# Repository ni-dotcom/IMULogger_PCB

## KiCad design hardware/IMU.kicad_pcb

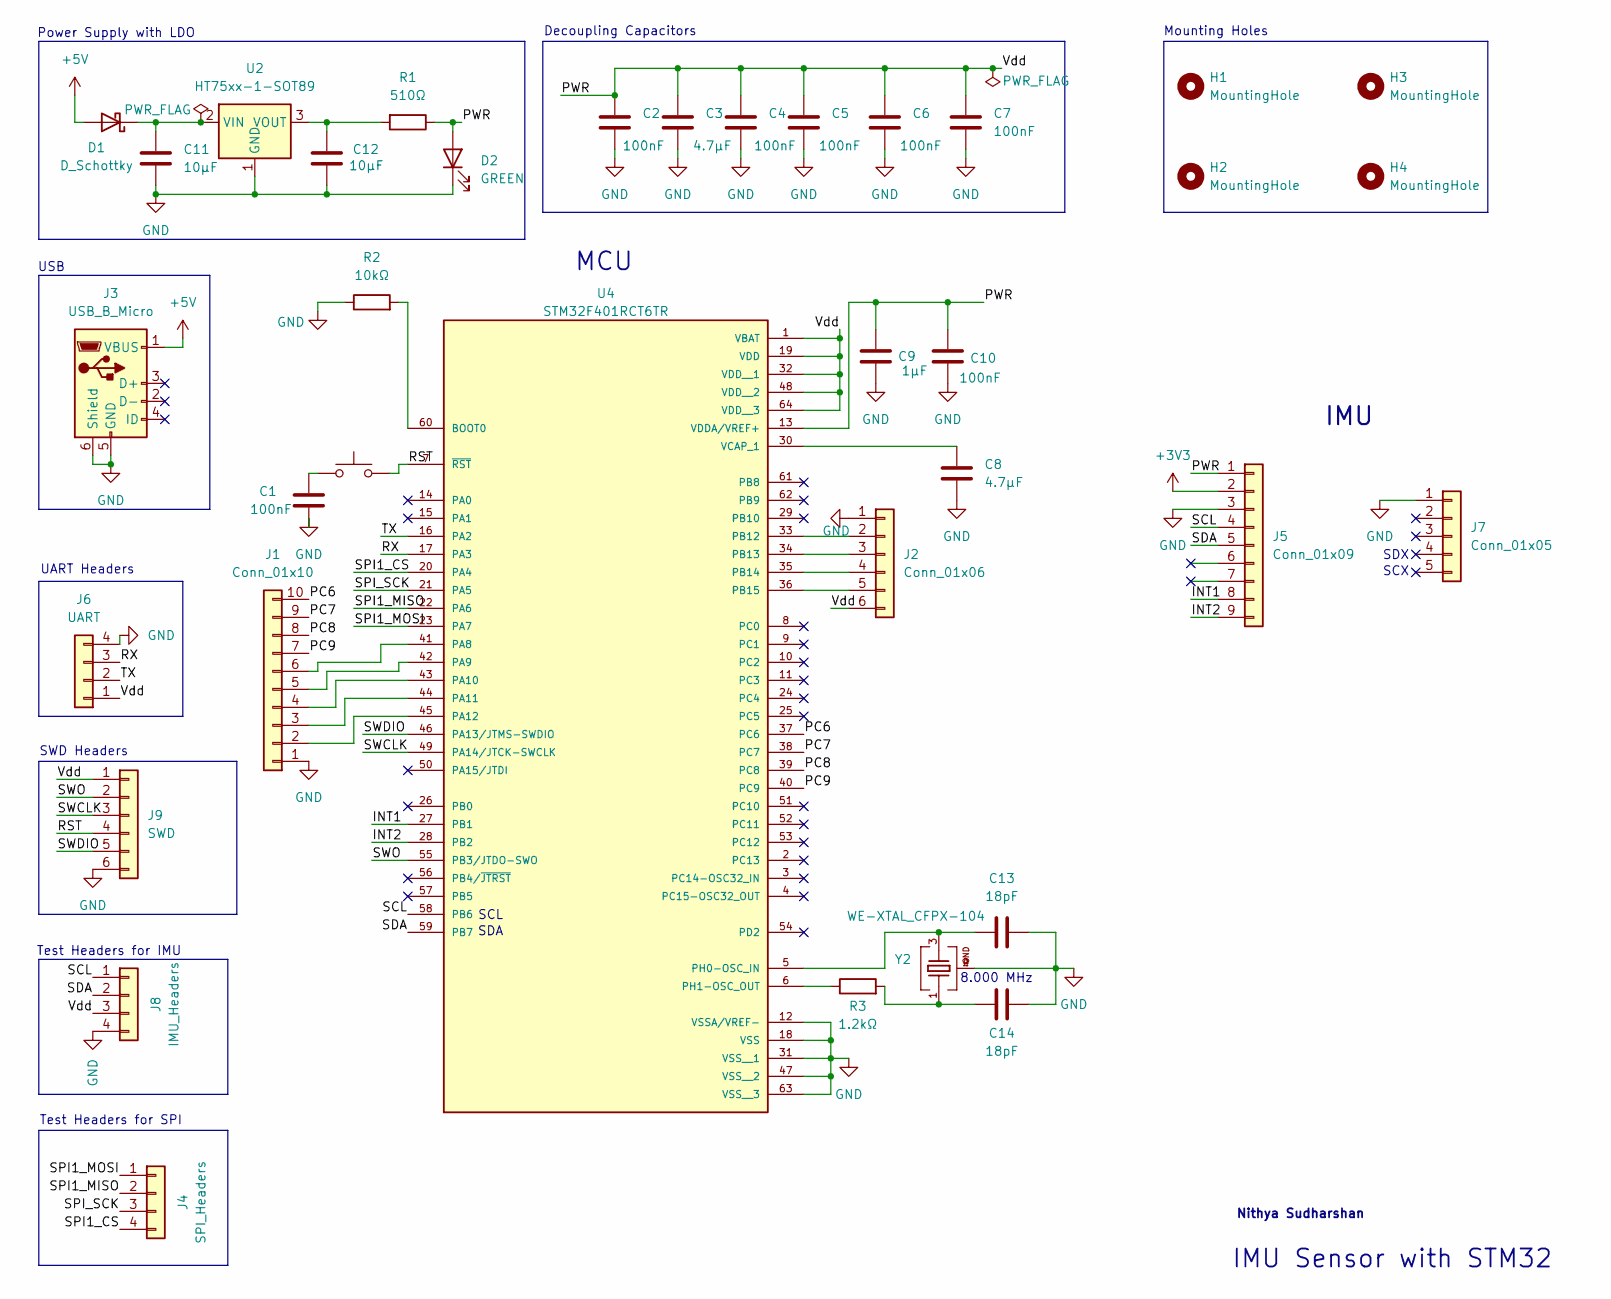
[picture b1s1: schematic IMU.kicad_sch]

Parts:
C1, C2, C4, C5, C6, C7, C10: 100nF; C_0805_2012Metric
C3, C8: 4.7μF; C_0805_2012Metric
C9: 1μF; C_0805_2012Metric
C11, C12: 10μF; C_0805_2012Metric
C13, C14: 18pF; C_0805_2012Metric
D1: D_Schottky; D_3220_8050Metric
D2: GREEN; LED_0805_2012Metric
H1, H2, H3, H4: MountingHole; MountingHole_2.7mm_M2.5_Pad
J1: Conn_01x10; PinHeader_1x10_P2.54mm_Vertical
J2: Conn_01x06; PinHeader_1x06_P2.54mm_Vertical
J3: USB_B_Micro; USB_Micro-B_GCT_USB3076-30-A
J4: SPI_Headers; PinHeader_1x04_P2.54mm_Vertical
J5: Conn_01x09; PinHeader_1x09_P2.54mm_Vertical
J6: UART; PinHeader_1x04_P2.54mm_Vertical
J7: Conn_01x05; PinHeader_1x05_P2.54mm_Vertical
J8: IMU_Headers; PinHeader_1x04_P2.54mm_Vertical
J9: SWD; PinHeader_1x06_P2.54mm_Vertical
R1: 510Ω; R_0805_2012Metric
R2: 10kΩ; R_0805_2012Metric
R3: 1.2kΩ; R_0805_2012Metric
SW1: SW_Push; SW_SPST_PTS647_Sx38
U2: HT75xx-1-SOT89; SOT-89-3
U4: STM32F401RCT6TR; STM32F4QFP50P1200X1200X160-64N; PARTREV 11
Y2: WE-XTAL_CFPX-104

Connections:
+3V3: J5.2; also elsewhere on the board
+5V: D1.2 (A), J3.1 (VBUS)
/INT1: J5.8, U4.27 (PB1)
/INT2: J5.9, U4.28 (PB2)
/PC6: J1.10, U4.37 (PC6)
/PC7: J1.9, U4.38 (PC7)
/PC8: J1.8, U4.39 (PC8)
/PC9: J1.7, U4.40 (PC9)
/PWR: C2.1, C3.1, C4.1, C5.1, C6.1, C7.1, C9.1, C10.1, D2.2 (A), J2.6, J5.1, J6.1, J8.3, J9.1, R1.1, U4.1 (VBAT), U4.13 (VDDA/VREF+), U4.19 (VDD), U4.32 (VDD__1), U4.48 (VDD__2), U4.64 (VDD__3)
/RST: J9.4, SW1.2, U4.7 (~RST)
/RX: J6.3, U4.17 (PA3)
/SCL: J5.4, J8.1, U4.58 (PB6)
/SDA: J5.5, J8.2, U4.59 (PB7)
/SPI1_CS: J4.4, U4.20 (PA4)
/SPI1_MISO: J4.2, U4.22 (PA6)
/SPI1_MOSI: J4.1, U4.23 (PA7)
/SPI_SCK: J4.3, U4.21 (PA5)
/SWCLK: J9.3, U4.49 (PA14/JTCK-SWCLK)
/SWDIO: J9.5, U4.46 (PA13/JTMS-SWDIO)
/SWO: J9.2, U4.55 (PB3/JTDO-SWO)
/TX: J6.2, U4.16 (PA2)
GND: C1.2, C2.2, C3.2, C4.2, C5.2, C6.2, C7.2, C8.2, C9.2, C10.2, C11.2, C12.2, C13.2, C14.1, D2.1 (K), J1.1, J2.1, J3.5 (GND), J3.6 (Shield), J5.3, J6.4, J7.1, J8.4, J9.6, R2.1, U2.1 (GND), U4.12 (VSSA/VREF-), U4.18 (VSS), U4.31 (VSS__1), U4.47 (VSS__2), U4.63 (VSS__3), Y2.2, Y2.4
unnamed 22: C1.1, SW1.1; also elsewhere on the board
unnamed: C14.2, R3.2, Y2.1
unnamed: C11.1, D1.1 (K), U2.2 (VIN)
unnamed: J1.2, U4.45 (PA12)
unnamed: J1.3, U4.44 (PA11)
unnamed: J1.4, U4.43 (PA10)
unnamed: J1.5, U4.42 (PA9)
unnamed: J1.6, U4.41 (PA8)
unnamed: J2.2, U4.33 (PB12)
unnamed: J2.3, U4.34 (PB13)
unnamed: J2.4, U4.35 (PB14)
unnamed: J2.5, U4.36 (PB15)
unnamed: C12.1, R1.2, U2.3 (VOUT)
unnamed: R2.2, U4.60 (BOOT0)
unnamed: C13.1, U4.5 (PH0-OSC_IN), Y2.3
unnamed: R3.1, U4.6 (PH1-OSC_OUT)
unnamed: C8.1, U4.30 (VCAP_1)

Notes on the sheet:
SDA
SCL
IMU Sensor with STM32
Mounting Holes
8.000 MHz
Power Supply with LDO
SDX
Nithya Sudharshan
SWD Headers
Test Headers for IMU
USB
MCU
SCX
Decoupling Capacitors
Test Headers for SPI
IMU
UART Headers

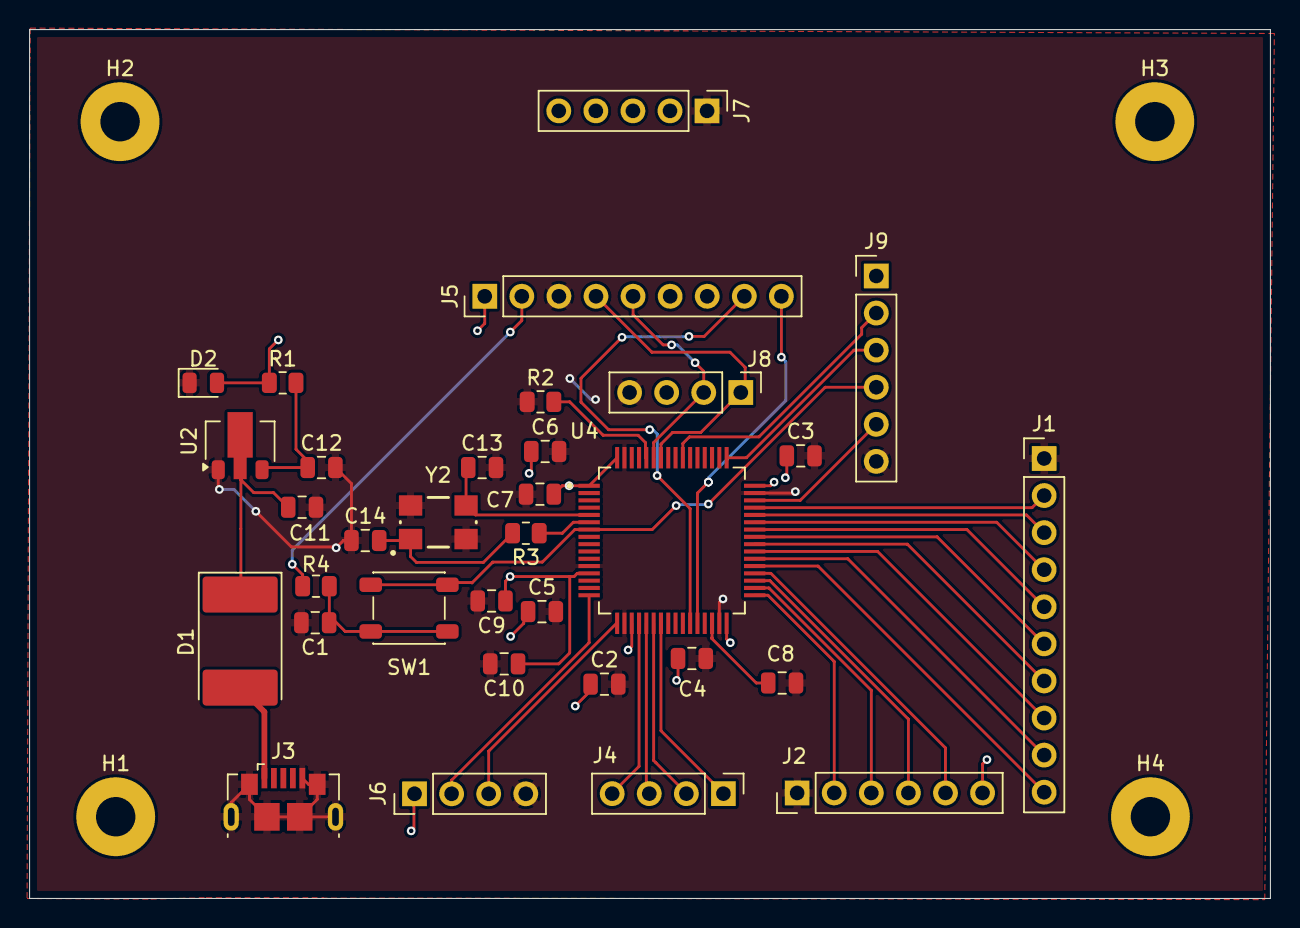
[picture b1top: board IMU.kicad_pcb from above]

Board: 2 copper layers, 85.0 x 59.5 mm, 37 parts (0 on the bottom side), 39 nets.

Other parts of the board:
R4: 10k?; R_0805_2012Metric

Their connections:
+3V3: R4.2; also elsewhere on the board
unnamed 22: R4.1; also elsewhere on the board

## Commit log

2026-03-09 fix changes
2026-03-09 moved some stuff
2026-03-09 fixed files
2026-03-10 first draft; normalized line endings
2026-03-10 first draft
2026-03-11 first draft schematic
2026-03-11 added clock and other stuff
2026-03-12 fixed crystal and misc
2026-03-12 more changes
2026-03-14 added footprints
2026-03-14 (mostly) fixed ERC
2026-03-14 layout first draft
2026-03-16 layout
2026-03-17 layout completed
2026-03-19 fixed errors
2026-03-21 added spi
2026-03-22 Fixed IMU
2026-03-22 finished layout
2026-05-14 Initial code
